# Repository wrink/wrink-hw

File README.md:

# wrink-hw

Hardware for **wrink**, a low-power wireless sensor network with a
purpose-built IPv6 network stack running on FreeRTOS.

The projects here are [KiCad](https://www.kicad.org/) projects, supported by
[kifab](https://github.com/pengi/kifab). kifab vendors the fab's parts
libraries into each project, applies the fab's design rules, runs DRC, and
generates the gerber, BOM and placement files needed to order the boards.

## Projects

### [rpi-nrf52840-hat](rpi-nrf52840-hat/)

A Raspberry Pi HAT with an nRF52840 microcontroller (E73-2G4M08S1C module).
It is intended as a wrink gateway, bridging the Raspberry Pi and the wireless
network, but it can be used for anything that needs an nRF52840 on a
Raspberry Pi.

<p align="center"></p>

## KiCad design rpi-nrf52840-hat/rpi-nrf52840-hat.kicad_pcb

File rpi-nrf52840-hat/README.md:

# rpi-nrf52840-hat

<!-- kifab:begin (generated by `kifab readme`; edits in here are lost) -->

## PCB

## Schematic

## Bill of materials

| Qty | Value | References | Footprint | Part |
| ---: | --- | --- | --- | --- |
| 2 | 4.7uF | C1, C5 | C0805 | [C20416422](https://www.lcsc.com/product-detail/C20416422.html), TCC0805X7R475K500FT |
| 2 | 18pF | C2, C3 | C0603 | [C1647](https://www.lcsc.com/product-detail/C1647.html), CL10C180JB8NNNC |
| 1 | RGB_CA | D1 | LED_RGB_1.6x1.5mm_CA_P4-1615 | [C7496855](https://www.lcsc.com/product-detail/C7496855.html), P4-1615G2B2R4TS2-06T-001-24 |
| 2 | Conn_02x04_Odd_Even | J1, J3 | PinHeader_2x04_P2.54mm_Vertical | [C41413841](https://www.lcsc.com/product-detail/C41413841.html), A254UP-ZS04P |
| 1 | Raspberry_Pi_4 | J2 | PinSocket_2x20_P2.54mm_Vertical | [C19725278](https://www.lcsc.com/product-detail/C19725278.html), HDGCPH2.54-PZS-2X20 |
| 11 | 330Ω | R1, R2, R3, R4, R5, R6, R7, R8, R12, R13, R15 | R0603 | [C23138](https://www.lcsc.com/product-detail/C23138.html), 0603WAF3300T5E |
| 1 | 4.7kΩ | R11 | R0603 | [C23162](https://www.lcsc.com/product-detail/C23162.html), 0603WAF4701T5E |
| 1 | E73-2G4M08S1C | U1 | WIRELM-SMD_E73-2G4M08S1C | [C356849](https://www.lcsc.com/product-detail/C356849.html) |
| 1 | 24C32 | U2 | SOP-8_L4.9-W3.9-P1.27-LS6.0-BL | [C18723546](https://www.lcsc.com/product-detail/C18723546.html), 24C32BN(XBLW) |
| 1 | 32.768kHz 12.5pF | X1 | CRYSTAL-SMD_L3.2-W1.5-1 | [C7462182](https://www.lcsc.com/product-detail/C7462182.html) |

<!-- kifab:end -->

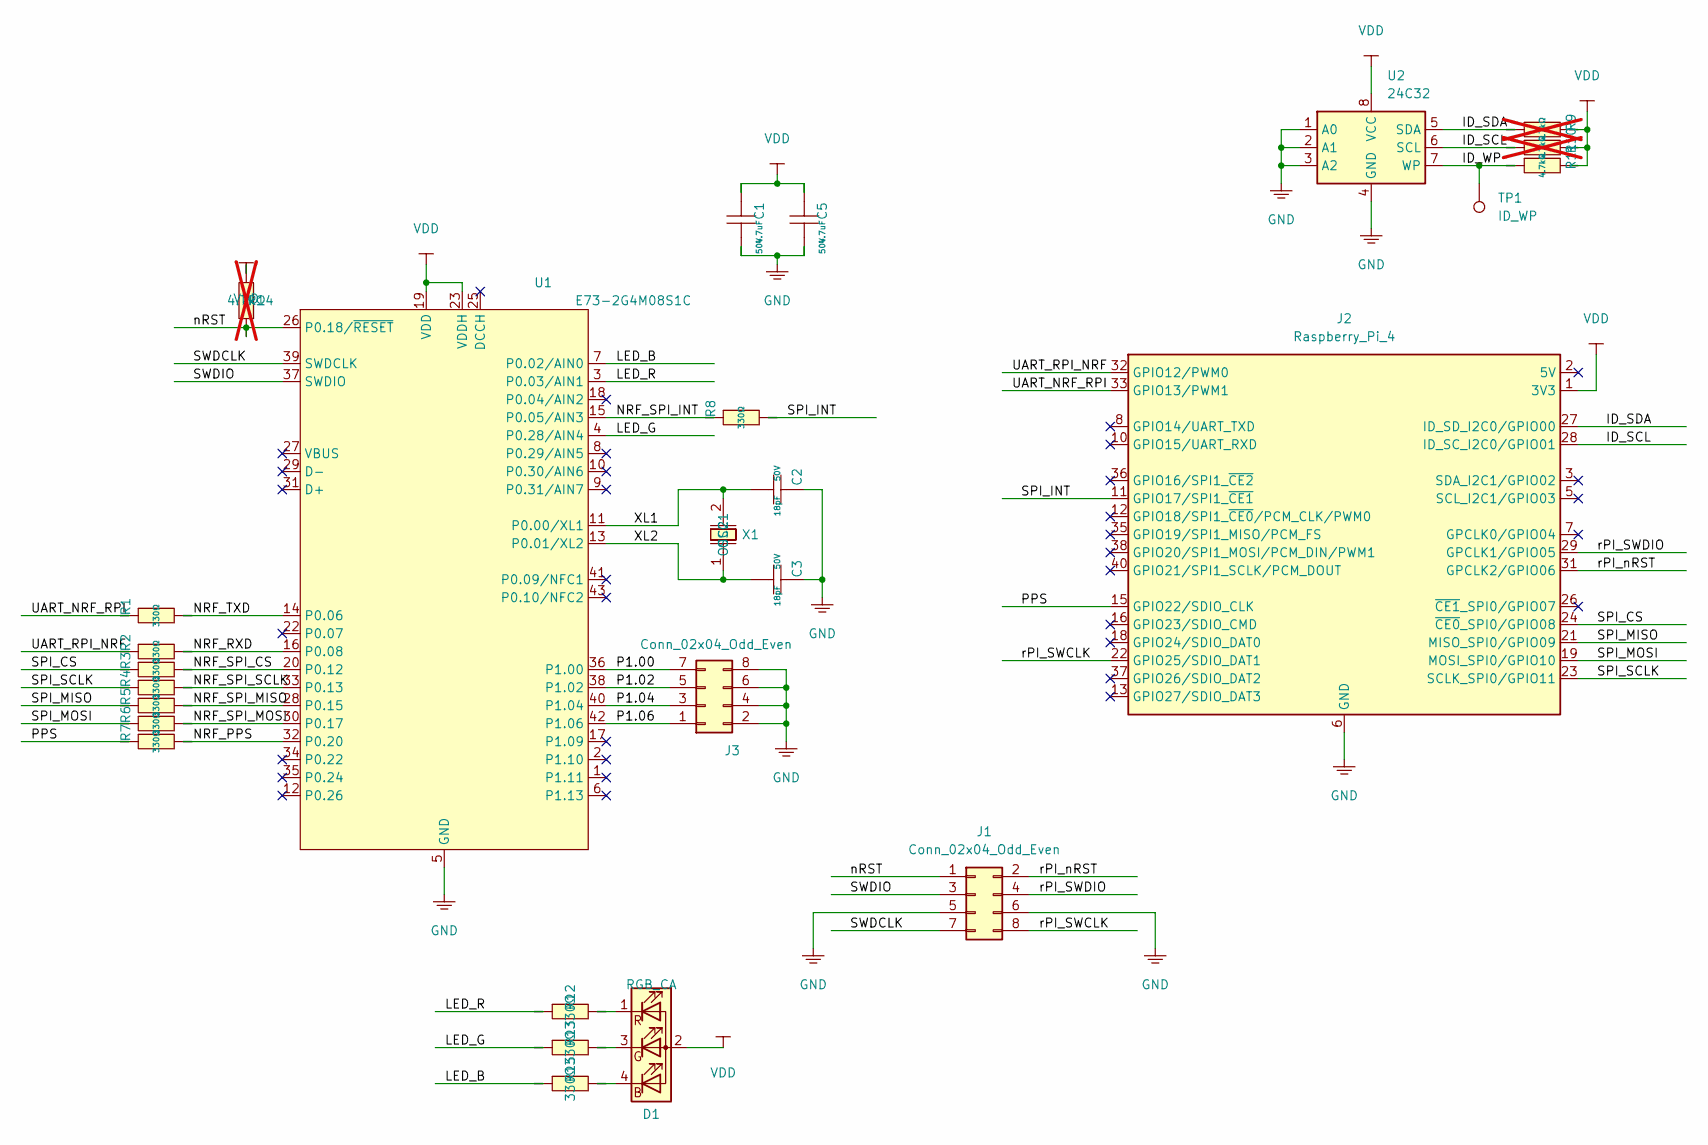
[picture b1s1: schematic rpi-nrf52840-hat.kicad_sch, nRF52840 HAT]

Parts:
C1, C5: 4.7uF; C0805; Voltage Rated 50V; Tolerance ±10%; Part TCC0805X7R475K500FT; LCSC C20416422
C2, C3: 18pF; C0603; Voltage Rated 50V; Tolerance ±5%; Part CL10C180JB8NNNC; LCSC C1647
D1: RGB_CA; LED_RGB_1.6x1.5mm_CA_P4-1615; MPN P4-1615G2B2R4TS2-06T-001-24; LCSC C7496855
J1, J3: Conn_02x04_Odd_Even; PinHeader_2x04_P2.54mm_Vertical; MPN A254UP-ZS04P; LCSC C41413841
J2: Raspberry_Pi_4; PinSocket_2x20_P2.54mm_Vertical; MPN HDGCPH2.54-PZS-2X20; LCSC C19725278
R1, R2, R3, R4, R5, R6, R7, R8, R12, R13, R15: 330Ω; R0603; MPN 0603WAF3300T5E; LCSC C23138
R9, R10, R14: 4.7kΩ; R0603; MPN 0603WAF4701T5E; LCSC C23162; not fitted
R11: 4.7kΩ; R0603; MPN 0603WAF4701T5E; LCSC C23162
TP1: ID_WP; PinHeader_1x01_P2.54mm_Vertical
U1: E73-2G4M08S1C; WIRELM-SMD_E73-2G4M08S1C; LCSC C356849
U2: 24C32; SOP-8_L4.9-W3.9-P1.27-LS6.0-BL; MPN 24C32BN(XBLW); LCSC C18723546
X1: 32.768kHz 12.5pF; CRYSTAL-SMD_L3.2-W1.5-1; Frequency Tolerance ±20ppm; Part CC7V-T1A-32.768KHZ-12.5PF-20PPM-TA-QC; LCSC C7462182

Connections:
/ID_SCL: J2.28 (ID_SC_I2C0/GPIO01), R10.1, U2.6 (SCL)
/ID_SDA: J2.27 (ID_SD_I2C0/GPIO00), R9.1, U2.5 (SDA)
/ID_WP: R11.1, TP1.1 (1_1), U2.7 (WP)
/LED_B: R15.1, U1.7 (P0.02/AIN0)
/LED_G: R13.1, U1.4 (P0.28/AIN4)
/LED_R: R12.1, U1.3 (P0.03/AIN1)
/NRF_PPS: R7.2, U1.32 (P0.20)
/NRF_RXD: R2.2, U1.16 (P0.08)
/NRF_SPI_CS: R3.2, U1.20 (P0.12)
/NRF_SPI_INT: R8.1, U1.15 (P0.05/AIN3)
/NRF_SPI_MISO: R5.2, U1.28 (P0.15)
/NRF_SPI_MOSI: R6.2, U1.30 (P0.17)
/NRF_SPI_SCLK: R4.2, U1.33 (P0.13)
/NRF_TXD: R1.2, U1.14 (P0.06)
/P1.00: J3.7, U1.36 (P1.00)
/P1.02: J3.5, U1.38 (P1.02)
/P1.04: J3.3, U1.40 (P1.04)
/P1.06: J3.1, U1.42 (P1.06)
/PPS: J2.15 (GPIO22/SDIO_CLK), R7.1
/SPI_CS: J2.24 (~CE0_SPI0/GPIO08), R3.1
/SPI_INT: J2.11 (GPIO17/SPI1_~CE1), R8.2
/SPI_MISO: J2.21 (MISO_SPI0/GPIO09), R5.1
/SPI_MOSI: J2.19 (MOSI_SPI0/GPIO10), R6.1
/SPI_SCLK: J2.23 (SCLK_SPI0/GPIO11), R4.1
/SWDCLK: J1.7, U1.39 (SWDCLK)
/SWDIO: J1.3, U1.37 (SWDIO)
/UART_NRF_RPI: J2.33 (GPIO13/PWM1), R1.1
/UART_RPI_NRF: J2.32 (GPIO12/PWM0), R2.1
/XL1: C2.2, U1.11 (P0.00/XL1), X1.2
/XL2: C3.2, U1.13 (P0.01/XL2), X1.1
/nRST: J1.1, R14.2, U1.26 (P0.18/~RESET)
/rPI_SWCLK: J1.8, J2.22 (GPIO25/SDIO_DAT1)
/rPI_SWDIO: J1.4, J2.29 (GPCLK1/GPIO05)
/rPI_nRST: J1.2, J2.31 (GPCLK2/GPIO06)
GND: C1.2, C2.1, C3.1, C5.2, J1.5, J1.6, J2.6 (GND), J2.9 (GND), J2.14 (GND), J2.20 (GND), J2.25 (GND), J2.30 (GND), J2.34 (GND), J2.39 (GND), J3.2, J3.4, J3.6, J3.8, U1.5 (GND), U1.21 (GND), U1.24 (GND), U2.1 (A0), U2.2 (A1), U2.3 (A2), U2.4 (GND)
unnamed: D1.4 (BK), R15.2
unnamed: D1.3 (GK), R13.2
unnamed: D1.1 (RK), R12.2
VDD: C1.1, C5.1, D1.2 (A), J2.1 (3V3), J2.17 (3V3), R9.2, R10.2, R11.2, R14.1, U1.19 (VDD), U1.23 (VDDH), U2.8 (VCC)

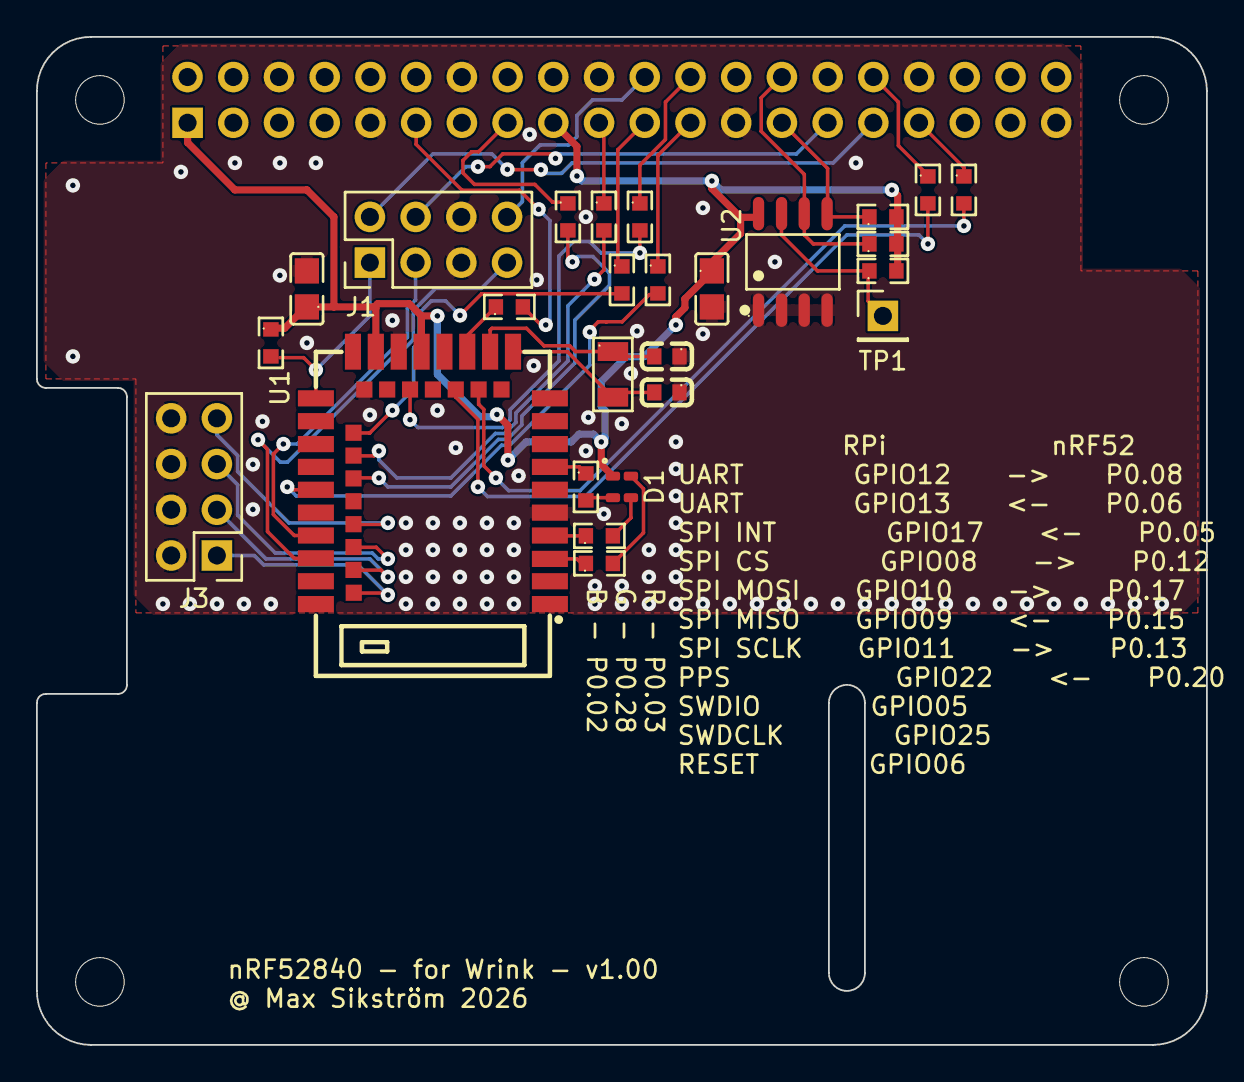
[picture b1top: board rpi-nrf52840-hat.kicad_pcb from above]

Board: 2 copper layers, 65.0 x 56.0 mm, 31 parts (1 on the bottom side), 39 nets.

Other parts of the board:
MH1, MH2, MH3, MH4: MountingHole_2.7mm_M2.5
